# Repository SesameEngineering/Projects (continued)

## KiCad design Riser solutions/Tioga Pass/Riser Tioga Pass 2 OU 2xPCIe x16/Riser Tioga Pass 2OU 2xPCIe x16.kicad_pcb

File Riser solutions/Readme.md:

#Riser Solutions

##Riser solutions for Leopard

###Riser 2 OU, 6x Oculink connector

On this riser we have 6 Oculink connector. Each connector is connected to 4 PCie lanes so we use the 24 PCie lanes available from Leopard server. This riser is used for storage solution since we can connect up to 6 U.2 form factor drives. A special cable, Oculink to U.2 has to be used to connect to each drives. 

###Riser 2 OU, 1x connector PCIe x16 + 2x Oculink connector

On this riser we have 2 Oculink connector and one x16 PCIe connector. Each Oculink uses 4 PCIe lanes so in total we use the 24 PCIe lanes available from Leopard server. Oculink connectors can be connected to U.2 devices via a Oculink to U.2 cable. Any half length PCIe devices can be connected to the x16 PCIe connector (Ava Board, network card, HBA, small form factor GPUs, etc..).

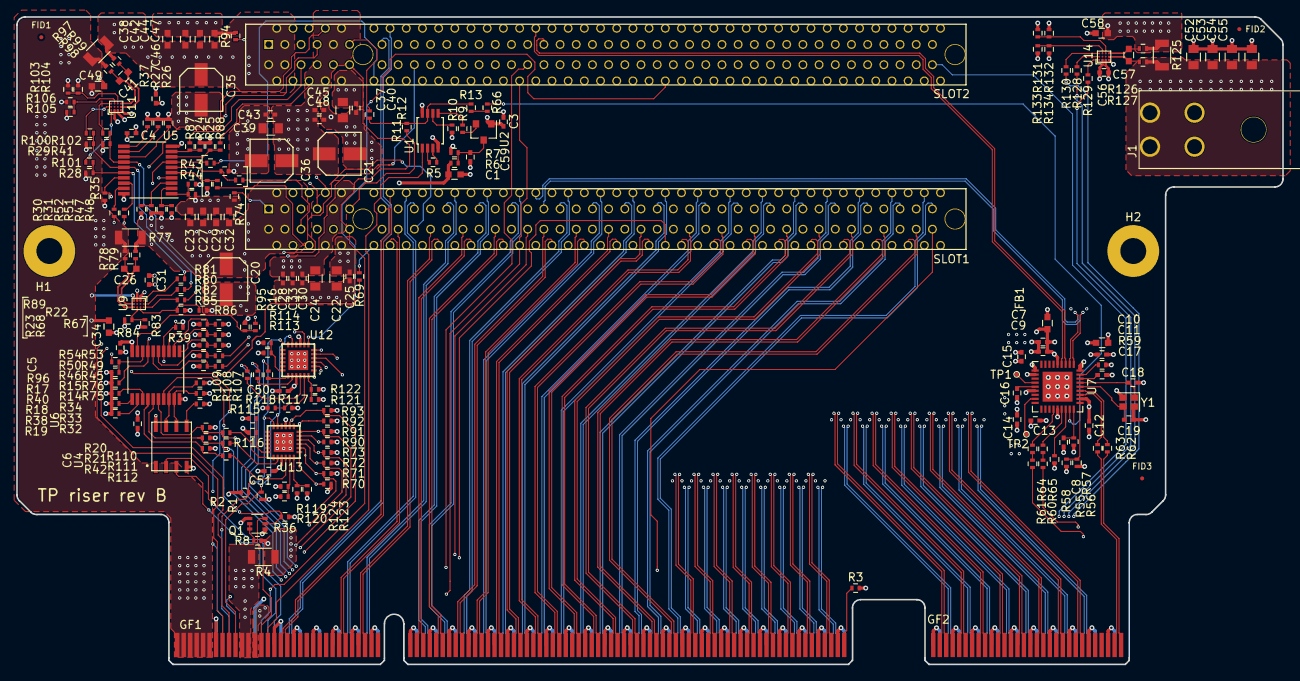
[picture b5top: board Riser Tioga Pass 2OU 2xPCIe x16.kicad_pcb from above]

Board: 6 copper layers, 156.4 x 80.0 mm, 218 parts (0 on the bottom side), 274 nets.

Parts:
C1, C23, C26, C27, C29, C32, C34, C38, C41, C42, C44, C47, C49, C56, C58: 0.1u 25V; C_0603
C3, C4, C5, C6, C8, C25, C28, C30, C31, C33, C40, C43, C45, C46, C48, C50, C51, C57: 0.1u 16V; C_0402
C7: 1u 6.3V; C_0402
C9, C11, C12, C13, C14, C15: 1u 10V; C_0402
C10: 2.2u 10V; C_0603
C16, C17: 0.1u 10V; C_0402
C18, C19: 18p 50V; C_0402
C20, C21, C35, C36: 100u 16V; CapaElec_100u_16V_5.3x5.3mm
C22, C24, C37, C39: 10u 6.3V; C_0805
C52, C53, C54, C55: 22u 16V; C_0805
C59: 0.01u 16V; C_0402
FB1: 300 Ohm 0.5A; Ferrite_0603
FID1, FID2, FID3: Fiducial; Fiducial_0.5mm_Dia_1mm_Outer
GF1: TiogaPass_GF1; GoldFinger_Samtec_HSEC8-1XXX_200pins
GF2: TiogaPAss_GF2; GoldFinger_Samtec_HSEC8-1XXX_60pins
H1, H2: MountingHole_Pad; MountingHole_3.2mm_M3_Pad
J1: RA_4pins_ATX; Conn_02x02_RA_4.2mm_MiniFitJr
Q1: 2N7002KDW; SOT-363_SC-70-6
R1, R2: 475; R_0402
R3: 100; R_0402
R4: 0; R_1206
R5, R9, R11, R12, R13, R30, R31, R60, R61, R62, R63, R64, R65, R66, R67, R68, R69, R74, R75, R76, R80, R81, R82, R87, R88, R89, R94, R95, R96, R100, R101, R102, R107, R108, R109, R110, R111, R112, R128, R129, R130: 0; R_0402
R6: 8.2k; R_0402
R7: 3.3k; R_0402
R8, R10, R14, R15, R16, R17, R18, R19, R20, R21, R22, R23, R24, R25, R26, R27, R28, R29, R33, R34, R70, R71, R72, R73, R90, R91, R92, R93: 4.7k; R_0402
R32, R35, R36, R37, R38, R39, R40, R41, R42, R43, R44, R45, R46, R47, R48, R49, R50, R51, R52, R53, R54, R57, R83, R84, R85, R86, R103, R104, R105, R106, R113, R114, R115, R116, R117, R118, R119, R120, R121, R122, R123, R124, R131, R132, R133, R134: 10k; R_0402
R55, R56, R58: 100k; R_0402
R59: 12k; R_0402
R77, R97, R125: 0.002; R_1206
R78, R79, R98, R99, R126, R127: 10; R_0402
SLOT1, SLOT2: x16_PCIe_Conn; pcie_16x
TP1: OCS_N1; TestPoint_Pad_D0.5mm
TP2: OCS_N2; TestPoint_Pad_D0.5mm
U1: 74LVC2G08DP-Q100H; TSSOP-8_3x3mm_Pitch0.65mm
U2: TPS3809K33; SOT-23
U4: PCA9515AD,118; SO-8_4.9mmx3.9mm
U5, U6: PCA9544APWR; TSSOP-20_4.4x6.5mm_Pitch0.65mm
U7: USB2512BI-AEZG; QFN-36-1EP_6x6mm_Pitch0.5mm
U9, U11, U14: INA231AIYFFT; DSBGA-12_1.65x1.39mm_Pitch0.4mm
U12, U13: PI4IOE5V9535ZDEX; TQFN-24_4x4mm_Pitch0.5mm
Y1: XTAL 24Mhz; Crystal_SMD_2016-4pin_2.0x1.6mm

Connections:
+3V3: C21.1, C24.1, C28.1, C30.1, C33.1, C36.1, C39.1, C43.1, C45.1, C48.1, R4.1, R8.2, R10.2, SLOT1.A9, SLOT1.A10, SLOT1.B8, SLOT2.A9, SLOT2.A10, SLOT2.B8
+3V3_MB: GF1.21, GF1.22, GF1.23, GF1.24, R4.2
+3V3_STBY: C3.2, C4.1, C5.1, C6.1, C22.1, C25.1, C31.1, C37.1, C40.1, C46.1, C50.1, C51.1, C57.1, FB1.2, GF1.25, R14.1, R15.1, R16.1, R17.1, R18.1, R19.1, R20.1, R21.1, R22.1, R23.1, R24.1, R25.1, R26.1, R27.1, R28.1, R29.1, R32.1, R33.1, R34.1, R35.1, R36.1, R37.1, R38.1, R39.1, R40.1, R41.1, R42.1, R43.1, R45.1, R47.1, R49.1, R51.1, R53.1, R70.1, R71.1, R72.1, R73.1, R83.1, R85.1, R90.1, R91.1, R92.1, R93.1, R103.1, R105.1, R113.1, R115.1, R117.1, R119.1, R121.1, R123.1, R131.1, R133.1, SLOT1.B10, SLOT2.B10, U1.8, U4.8, U5.20, U6.20, U9.B1, U11.B1, U12.21, U13.21, U14.B1
+3V3_USB_HUB: C7.1, C9.1, C10.1, C11.1, C12.1, C13.1, C14.1, C15.1, FB1.1, R55.1, R57.1, U7.5, U7.10, U7.15, U7.23, U7.29, U7.36
+12V: C1.1, C34.1, C49.1, C58.1, GF1.1, GF1.2, GF1.3, GF1.4, GF1.5, GF1.6, GF1.7, GF1.8, GF1.9, GF1.10, GF1.11, GF1.12, R6.1, R77.2, R78.2, R97.1, R98.2, R125.1, R126.2, U9.D1, U11.D1, U14.D1
+12V_ATX: C52.1, C53.1, C54.1, C55.1, J1.3, J1.4, R125.2, R127.2
+12V_SLOT2: C20.1, C23.1, C27.1, C29.1, C32.1, R77.1, R79.2, SLOT1.A2, SLOT1.A3, SLOT1.B1, SLOT1.B2, SLOT1.B3
+12V_SLOT3: C35.1, C38.1, C42.1, C44.1, C47.1, R97.2, R99.2, SLOT2.A2, SLOT2.A3, SLOT2.B1, SLOT2.B2, SLOT2.B3
/ATX Power/ATX_P12V_SENSE_R_V+: C56.1, R126.1, U14.D3
/ATX Power/ATX_P12V_SENSE_R_V-: C56.2, R127.1, U14.D2
/ATX Power/ATX_VMONITOR_A0: R133.2, R134.1, U14.B3
/ATX Power/ATX_VMONITOR_A1: R131.2, R132.1, U14.C3
/GPIO expander/GPIO_B_EXP_A0: R113.2, R114.1, U12.18
/GPIO expander/GPIO_B_EXP_A1: R117.2, R118.1, U12.23
/GPIO expander/GPIO_B_EXP_A2: R121.2, R122.1, U12.24
/GPIO expander/GPIO_P_EXP_A0: R115.2, R116.1, U13.18
/GPIO expander/GPIO_P_EXP_A1: R119.2, R120.1, U13.23
/GPIO expander/GPIO_P_EXP_A2: R123.2, R124.1, U13.24
/Golden Finger/PERST_N_1: R5.2, U1.3
/Golden Finger/PERST_SLOT_N: R11.2, R12.2, R13.2, U1.7
/SMBUS MUX/SMB_B_HUB_A0: R43.2, R44.1, U5.1
/SMBUS MUX/SMB_B_HUB_A1: R47.2, R48.1, U5.2
/SMBUS MUX/SMB_B_HUB_A2: R51.2, R52.1, U5.3
/SMBUS MUX/SMB_P_HUB_A0: R45.2, R46.1, U6.1
/SMBUS MUX/SMB_P_HUB_A1: R49.2, R50.1, U6.2
/SMBUS MUX/SMB_P_HUB_A2: R53.2, R54.1, U6.3
/USB HUB/CFG_SEL1: R58.1, U7.25
/USB HUB/CRFILT: C16.1, U7.14
/USB HUB/NON_REM0: R55.2, R56.1, U7.28
/USB HUB/PLLFILT: C17.1, U7.34
/USB HUB/RBIAS: R59.1, U7.35
/USB HUB/SMCLK_USB_HUB: R60.1, R65.1
/USB HUB/SMDAT_USB_HUB: R61.1, R64.1
/USB HUB/USB2_P02_-R_D+: R62.1, U7.31
/USB HUB/USB2_P02_-R_D-: R63.1, U7.30
/USB HUB/USB_HUB_XTAL_IN: C18.1, U7.33, Y1.1
/USB HUB/USB_HUB_XTAL_OUT: C19.1, U7.32, Y1.3
/USB HUB/VBUS_DET: C8.1, R57.2, U7.27
/x16 PCIe Slot 2 (lower)/SLOT2_P12V_SENSE_R_V+: C26.1, R78.1, U9.D3
/x16 PCIe Slot 2 (lower)/SLOT2_P12V_SENSE_R_V-: C26.2, R79.1, U9.D2
/x16 PCIe Slot 2 (lower)/SLOT2_VMONITOR_A0: R85.2, R86.1, U9.B3
/x16 PCIe Slot 2 (lower)/SLOT2_VMONITOR_A1: R83.2, R84.1, U9.C3
/x16 PCIe Slot 3 (upper)/SLOT3_P12V_SENSE_R_V+: C41.1, R98.1, U11.D3
/x16 PCIe Slot 3 (upper)/SLOT3_P12V_SENSE_R_V-: C41.2, R99.1, U11.D2
/x16 PCIe Slot 3 (upper)/SLOT3_VMONITOR_A0: R105.2, R106.1, U11.B3
/x16 PCIe Slot 3 (upper)/SLOT3_VMONITOR_A1: R103.2, R104.1, U11.C3
CLK_100M_PCH_SLOTX24_S4_D+: GF1.36, SLOT2.A13
CLK_100M_PCH_SLOTX24_S4_D-: GF1.38, SLOT2.A14
CLK_100M_PCH_SLOTX24_S5_D+: GF1.33, SLOT1.A13
CLK_100M_PCH_SLOTX24_S5_D-: GF1.35, SLOT1.A14
FM_PE_SLOTX24_WAKE_N: GF1.28, SLOT1.B11, SLOT2.B11
FM_PRSNT_2_6_N: GF1.199, R3.1
FM_PWRBRK_SLOT_N: GF1.20, SLOT1.B30, SLOT2.B30
FM_SLT_CFG0: GF1.19, R1.1, U12.11, U13.11
FM_SLT_CFG1: GF1.18, R2.1, U12.12, U13.12
GND: C1.2, C3.1, C4.2, C5.2, C6.2, C7.2, C8.2, C9.2, C10.2, C11.2, C12.2, C13.2, C14.2, C15.2, C16.2, C17.2, C18.2, C19.2, C20.2, C21.2, C22.2, C23.2, C24.2, C25.2, C27.2, C28.2, C29.2, C30.2, C31.2, C32.2, C33.2, C34.2, C35.2, C36.2, C37.2, C38.2, C39.2, C40.2, C42.2, C43.2, C44.2, C45.2, C46.2, C47.2, C48.2, C49.2, C50.2, C51.2, C52.2, C53.2, C54.2, C55.2, C57.2, C58.2, C59.2, GF1.13, GF1.14, GF1.26, GF1.31, GF1.34, GF1.37, GF1.40, GF1.43, GF1.46, GF1.49, GF1.52, GF1.55, GF1.58, GF1.61, GF1.64, GF1.65, GF1.68, GF1.71, GF1.74, GF1.77, GF1.80, GF1.83, GF1.86, GF1.89, GF1.92, GF1.95, GF1.98, GF1.101, GF1.104, GF1.107, GF1.110, GF1.113, GF1.116, GF1.119, GF1.122, GF1.125, GF1.128, GF1.131, GF1.134, GF1.137, GF1.140, GF1.143, GF1.146, GF1.149, GF1.152, GF1.155, GF1.158, GF1.161, GF1.164, GF1.167, GF1.170, GF1.173, GF1.176, GF1.179, GF1.182, GF1.185, GF1.188, GF1.191, GF1.194, GF1.197, GF1.200, GF2.1, GF2.4, GF2.7, GF2.10, GF2.13, GF2.16, GF2.19, GF2.22, GF2.25, GF2.28, GF2.31, GF2.34, GF2.37, GF2.40, GF2.43, GF2.46, GF2.49, GF2.52, GF2.55, GF2.58, H1.1, H2.1, J1.1, J1.2, Q1.1, Q1.4, R1.2, R2.2, R3.2, R7.2, R44.2, R46.2, R48.2, R50.2, R52.2, R54.2, R56.2, R58.2, R59.2, R74.1, R84.2, R86.2, R94.1, R104.2, R106.2, R114.2, R116.2, R118.2, R120.2, R122.2, R124.2, R132.2, R134.2, SLOT1.A4, SLOT1.A12, SLOT1.A15, SLOT1.A18, SLOT1.A20, SLOT1.A23, SLOT1.A24, SLOT1.A27, SLOT1.A28, SLOT1.A31, SLOT1.A34, SLOT1.A37, SLOT1.A38, SLOT1.A41, SLOT1.A42, SLOT1.A45, SLOT1.A46, SLOT1.A49, SLOT1.A51, SLOT1.A54, SLOT1.A55, SLOT1.A58, SLOT1.A59, SLOT1.A62, SLOT1.A63, SLOT1.A66, SLOT1.A67, SLOT1.A70, SLOT1.A71, SLOT1.A74, SLOT1.A75, SLOT1.A78, SLOT1.A79, SLOT1.A82, SLOT1.B4, SLOT1.B7, SLOT1.B13, SLOT1.B16, SLOT1.B18, SLOT1.B21, SLOT1.B22, SLOT1.B25, SLOT1.B26, SLOT1.B29, SLOT1.B32, SLOT1.B35, SLOT1.B36, SLOT1.B39, SLOT1.B40, SLOT1.B43, SLOT1.B44, SLOT1.B47, SLOT1.B49, SLOT1.B52, SLOT1.B53, SLOT1.B56, SLOT1.B57, SLOT1.B60, SLOT1.B61, SLOT1.B64, SLOT1.B65, SLOT1.B68, SLOT1.B69, SLOT1.B72, SLOT1.B73, SLOT1.B76, SLOT1.B77, SLOT1.B80, SLOT2.A4, SLOT2.A12, SLOT2.A15, SLOT2.A18, SLOT2.A20, SLOT2.A23, SLOT2.A24, SLOT2.A27, SLOT2.A28, SLOT2.A31, SLOT2.A34, SLOT2.A37, SLOT2.A38, SLOT2.A41, SLOT2.A42, SLOT2.A45, SLOT2.A46, SLOT2.A49, SLOT2.A51, SLOT2.A54, SLOT2.A55, SLOT2.A58, SLOT2.A59, SLOT2.A62, SLOT2.A63, SLOT2.A66, SLOT2.A67, SLOT2.A70, SLOT2.A71, SLOT2.A74, SLOT2.A75, SLOT2.A78, SLOT2.A79, SLOT2.A82, SLOT2.B4, SLOT2.B7, SLOT2.B13, SLOT2.B16, SLOT2.B18, SLOT2.B21, SLOT2.B22, SLOT2.B25, SLOT2.B26, SLOT2.B29, SLOT2.B32, SLOT2.B35, SLOT2.B36, SLOT2.B39, SLOT2.B40, SLOT2.B43, SLOT2.B44, SLOT2.B47, SLOT2.B49, SLOT2.B52, SLOT2.B53, SLOT2.B56, SLOT2.B57, SLOT2.B60, SLOT2.B61, SLOT2.B64, SLOT2.B65, SLOT2.B68, SLOT2.B69, SLOT2.B72, SLOT2.B73, SLOT2.B76, SLOT2.B77, SLOT2.B80, U1.4, U2.1, U4.4, U5.10, U6.10, U7.11, U7.37, U9.C1, U11.C1, U12.9, U12.25, U13.9, U13.25, U14.C1, Y1.2, Y1.4
IRQ_OOB_MGMT_RISER_ALERT_N: GF1.16, R35.2, U5.17
unnamed: C59.1, R6.2, R7.1, U2.3
unnamed: Q1.5, Q1.6, R8.1
unnamed: R5.1, U1.2
unnamed: R9.1, U1.5
unnamed: R9.2, U2.2
unnamed: R10.1, U1.6
unnamed: R30.1, U5.19
unnamed: R31.1, U5.18
unnamed: R64.2, U7.22
unnamed: R65.2, U7.24
unnamed: R66.2, U7.26
unnamed: R67.1, SLOT1.B5
unnamed: R68.1, SLOT1.B6
unnamed: R69.1, SLOT1.B12
unnamed: R74.2, SLOT1.A1
unnamed: R75.2, SLOT1.A7
unnamed: R76.2, SLOT1.A8
unnamed: R80.1, U9.A2
unnamed: R81.1, U9.A1
unnamed: R82.2, U9.A3
unnamed: R87.1, SLOT2.B5
unnamed: R88.1, SLOT2.B6
unnamed: R89.1, SLOT2.B12
unnamed: R94.2, SLOT2.A1
unnamed: R95.2, SLOT2.A7
unnamed: R96.2, SLOT2.A8
unnamed: R100.1, U11.A2
unnamed: R101.1, U11.A1
unnamed: R102.2, U11.A3
unnamed: R107.2, U12.19
unnamed: R108.2, U12.20
unnamed: R109.2, U12.22
unnamed: R110.2, U13.19
unnamed: R111.2, U13.20
unnamed: R112.2, U13.22
unnamed: R128.1, U14.A2
unnamed: R129.1, U14.A1
unnamed: R130.2, U14.A3
unnamed: TP1.1, U7.13
unnamed: TP2.1, U7.17
P3E_CPU0_PE1_PCH_CON_RX8+: GF1.100, SLOT1.A47
P3E_CPU0_PE1_PCH_CON_RX8-: GF1.102, SLOT1.A48
P3E_CPU0_PE1_PCH_CON_RX9+: GF1.94, SLOT1.A43
P3E_CPU0_PE1_PCH_CON_RX9-: GF1.96, SLOT1.A44
P3E_CPU0_PE1_PCH_CON_RX10+: GF1.88, SLOT1.A39
P3E_CPU0_PE1_PCH_CON_RX10-: GF1.90, SLOT1.A40
P3E_CPU0_PE1_PCH_CON_RX11+: GF1.82, SLOT1.A35
P3E_CPU0_PE1_PCH_CON_RX11-: GF1.84, SLOT1.A36
P3E_CPU0_PE1_PCH_CON_RX12+: GF1.76, SLOT1.A29
P3E_CPU0_PE1_PCH_CON_RX12-: GF1.78, SLOT1.A30
P3E_CPU0_PE1_PCH_CON_RX13+: GF1.70, SLOT1.A25
P3E_CPU0_PE1_PCH_CON_RX13-: GF1.72, SLOT1.A26
P3E_CPU0_PE1_PCH_CON_RX14+: GF1.60, SLOT1.A21
P3E_CPU0_PE1_PCH_CON_RX14-: GF1.62, SLOT1.A22
P3E_CPU0_PE1_PCH_CON_RX15+: GF1.54, SLOT1.A16
P3E_CPU0_PE1_PCH_CON_RX15-: GF1.56, SLOT1.A17
P3E_CPU0_PE1_PCH_CON_TX8+: GF1.97, SLOT1.B45
P3E_CPU0_PE1_PCH_CON_TX8-: GF1.99, SLOT1.B46
P3E_CPU0_PE1_PCH_CON_TX9+: GF1.91, SLOT1.B41
P3E_CPU0_PE1_PCH_CON_TX9-: GF1.93, SLOT1.B42
P3E_CPU0_PE1_PCH_CON_TX10+: GF1.85, SLOT1.B37
P3E_CPU0_PE1_PCH_CON_TX10-: GF1.87, SLOT1.B38
P3E_CPU0_PE1_PCH_CON_TX11+: GF1.79, SLOT1.B33
P3E_CPU0_PE1_PCH_CON_TX11-: GF1.81, SLOT1.B34
P3E_CPU0_PE1_PCH_CON_TX12+: GF1.73, SLOT1.B27
P3E_CPU0_PE1_PCH_CON_TX12-: GF1.75, SLOT1.B28
P3E_CPU0_PE1_PCH_CON_TX13+: GF1.67, SLOT1.B23
P3E_CPU0_PE1_PCH_CON_TX13-: GF1.69, SLOT1.B24
P3E_CPU0_PE1_PCH_CON_TX14+: GF1.57, SLOT1.B19
P3E_CPU0_PE1_PCH_CON_TX14-: GF1.59, SLOT1.B20
P3E_CPU0_PE1_PCH_CON_TX15+: GF1.51, SLOT1.B14
P3E_CPU0_PE1_PCH_CON_TX15-: GF1.53, SLOT1.B15
P3E_CPU0_PE1_SS_C_RX0+: GF1.148, SLOT1.A80
P3E_CPU0_PE1_SS_C_RX0-: GF1.150, SLOT1.A81
P3E_CPU0_PE1_SS_C_RX1+: GF1.142, SLOT1.A76
P3E_CPU0_PE1_SS_C_RX1-: GF1.144, SLOT1.A77
P3E_CPU0_PE1_SS_C_RX2+: GF1.136, SLOT1.A72
P3E_CPU0_PE1_SS_C_RX2-: GF1.138, SLOT1.A73
P3E_CPU0_PE1_SS_C_RX3+: GF1.130, SLOT1.A68
P3E_CPU0_PE1_SS_C_RX3-: GF1.132, SLOT1.A69
P3E_CPU0_PE1_SS_C_RX4+: GF1.124, SLOT1.A64
P3E_CPU0_PE1_SS_C_RX4-: GF1.126, SLOT1.A65
P3E_CPU0_PE1_SS_C_RX5+: GF1.118, SLOT1.A60
P3E_CPU0_PE1_SS_C_RX5-: GF1.120, SLOT1.A61
P3E_CPU0_PE1_SS_C_RX6+: GF1.112, SLOT1.A56
P3E_CPU0_PE1_SS_C_RX6-: GF1.114, SLOT1.A57
P3E_CPU0_PE1_SS_C_RX7+: GF1.106, SLOT1.A52
P3E_CPU0_PE1_SS_C_RX7-: GF1.108, SLOT1.A53
P3E_CPU0_PE1_SS_C_TX0+: GF1.145, SLOT1.B78
P3E_CPU0_PE1_SS_C_TX0-: GF1.147, SLOT1.B79
P3E_CPU0_PE1_SS_C_TX1+: GF1.139, SLOT1.B74
P3E_CPU0_PE1_SS_C_TX1-: GF1.141, SLOT1.B75
P3E_CPU0_PE1_SS_C_TX2+: GF1.133, SLOT1.B70
P3E_CPU0_PE1_SS_C_TX2-: GF1.135, SLOT1.B71
P3E_CPU0_PE1_SS_C_TX3+: GF1.127, SLOT1.B66
P3E_CPU0_PE1_SS_C_TX3-: GF1.129, SLOT1.B67
P3E_CPU0_PE1_SS_C_TX4+: GF1.121, SLOT1.B62
P3E_CPU0_PE1_SS_C_TX4-: GF1.123, SLOT1.B63
P3E_CPU0_PE1_SS_C_TX5+: GF1.115, SLOT1.B58
P3E_CPU0_PE1_SS_C_TX5-: GF1.117, SLOT1.B59
P3E_CPU0_PE1_SS_C_TX6+: GF1.109, SLOT1.B54
P3E_CPU0_PE1_SS_C_TX6-: GF1.111, SLOT1.B55
P3E_CPU0_PE1_SS_C_TX7+: GF1.103, SLOT1.B50
P3E_CPU0_PE1_SS_C_TX7-: GF1.105, SLOT1.B51
P3E_CPU0_PE2_SS_C_RX0+: GF1.154, SLOT2.A16
P3E_CPU0_PE2_SS_C_RX0-: GF1.156, SLOT2.A17
P3E_CPU0_PE2_SS_C_RX1+: GF1.160, SLOT2.A21
P3E_CPU0_PE2_SS_C_RX1-: GF1.162, SLOT2.A22
P3E_CPU0_PE2_SS_C_RX2+: GF1.166, SLOT2.A25
P3E_CPU0_PE2_SS_C_RX2-: GF1.168, SLOT2.A26
P3E_CPU0_PE2_SS_C_RX3+: GF1.172, SLOT2.A29
P3E_CPU0_PE2_SS_C_RX3-: GF1.174, SLOT2.A30
P3E_CPU0_PE2_SS_C_RX4+: GF1.178, SLOT2.A35
P3E_CPU0_PE2_SS_C_RX4-: GF1.180, SLOT2.A36
P3E_CPU0_PE2_SS_C_RX5+: GF1.184, SLOT2.A39
P3E_CPU0_PE2_SS_C_RX5-: GF1.186, SLOT2.A40
P3E_CPU0_PE2_SS_C_RX6+: GF1.190, SLOT2.A43
P3E_CPU0_PE2_SS_C_RX6-: GF1.192, SLOT2.A44
P3E_CPU0_PE2_SS_C_RX7+: GF1.196, SLOT2.A47
P3E_CPU0_PE2_SS_C_RX7-: GF1.198, SLOT2.A48
P3E_CPU0_PE2_SS_C_RX8+: GF2.6, SLOT2.A52
P3E_CPU0_PE2_SS_C_RX8-: GF2.8, SLOT2.A53
P3E_CPU0_PE2_SS_C_RX9+: GF2.12, SLOT2.A56
P3E_CPU0_PE2_SS_C_RX9-: GF2.14, SLOT2.A57
P3E_CPU0_PE2_SS_C_RX10+: GF2.18, SLOT2.A60
P3E_CPU0_PE2_SS_C_RX10-: GF2.20, SLOT2.A61
P3E_CPU0_PE2_SS_C_RX11+: GF2.24, SLOT2.A64
P3E_CPU0_PE2_SS_C_RX11-: GF2.26, SLOT2.A65
P3E_CPU0_PE2_SS_C_RX12+: GF2.30, SLOT2.A68
P3E_CPU0_PE2_SS_C_RX12-: GF2.32, SLOT2.A69
P3E_CPU0_PE2_SS_C_RX13+: GF2.36, SLOT2.A72
P3E_CPU0_PE2_SS_C_RX13-: GF2.38, SLOT2.A73
P3E_CPU0_PE2_SS_C_RX14+: GF2.42, SLOT2.A76
P3E_CPU0_PE2_SS_C_RX14-: GF2.44, SLOT2.A77
P3E_CPU0_PE2_SS_C_RX15+: GF2.48, SLOT2.A80
P3E_CPU0_PE2_SS_C_RX15-: GF2.50, SLOT2.A81
P3E_CPU0_PE2_SS_C_TX0+: GF1.151, SLOT2.B14
P3E_CPU0_PE2_SS_C_TX0-: GF1.153, SLOT2.B15
P3E_CPU0_PE2_SS_C_TX1+: GF1.157, SLOT2.B19
P3E_CPU0_PE2_SS_C_TX1-: GF1.159, SLOT2.B20
P3E_CPU0_PE2_SS_C_TX2+: GF1.163, SLOT2.B23
P3E_CPU0_PE2_SS_C_TX2-: GF1.165, SLOT2.B24
P3E_CPU0_PE2_SS_C_TX3+: GF1.169, SLOT2.B27
P3E_CPU0_PE2_SS_C_TX3-: GF1.171, SLOT2.B28
P3E_CPU0_PE2_SS_C_TX4+: GF1.175, SLOT2.B33
P3E_CPU0_PE2_SS_C_TX4-: GF1.177, SLOT2.B34
P3E_CPU0_PE2_SS_C_TX5+: GF1.181, SLOT2.B37
P3E_CPU0_PE2_SS_C_TX5-: GF1.183, SLOT2.B38
P3E_CPU0_PE2_SS_C_TX6+: GF1.187, SLOT2.B41
P3E_CPU0_PE2_SS_C_TX6-: GF1.189, SLOT2.B42
P3E_CPU0_PE2_SS_C_TX7+: GF1.193, SLOT2.B45
P3E_CPU0_PE2_SS_C_TX7-: GF1.195, SLOT2.B46
P3E_CPU0_PE2_SS_C_TX8+: GF2.3, SLOT2.B50
P3E_CPU0_PE2_SS_C_TX8-: GF2.5, SLOT2.B51
P3E_CPU0_PE2_SS_C_TX9+: GF2.9, SLOT2.B54
P3E_CPU0_PE2_SS_C_TX9-: GF2.11, SLOT2.B55
P3E_CPU0_PE2_SS_C_TX10+: GF2.15, SLOT2.B58
P3E_CPU0_PE2_SS_C_TX10-: GF2.17, SLOT2.B59
P3E_CPU0_PE2_SS_C_TX11+: GF2.21, SLOT2.B62
P3E_CPU0_PE2_SS_C_TX11-: GF2.23, SLOT2.B63
P3E_CPU0_PE2_SS_C_TX12+: GF2.27, SLOT2.B66
P3E_CPU0_PE2_SS_C_TX12-: GF2.29, SLOT2.B67
P3E_CPU0_PE2_SS_C_TX13+: GF2.33, SLOT2.B70
P3E_CPU0_PE2_SS_C_TX13-: GF2.35, SLOT2.B71
P3E_CPU0_PE2_SS_C_TX14+: GF2.39, SLOT2.B74
P3E_CPU0_PE2_SS_C_TX14-: GF2.41, SLOT2.B75
P3E_CPU0_PE2_SS_C_TX15+: GF2.45, SLOT2.B78
P3E_CPU0_PE2_SS_C_TX15-: GF2.47, SLOT2.B79
PCIE_SLOT2_PRSNT2_1_N: R70.2, SLOT1.B17, U12.1, U13.1
PCIE_SLOT2_PRSNT2_2_N: R71.2, SLOT1.B31, U12.2, U13.2
PCIE_SLOT2_PRSNT2_3_N: R72.2, SLOT1.B48, U12.3, U13.3
PCIE_SLOT2_PRSNT2_4_N: R73.2, SLOT1.B81, U12.4, U13.4
PCIE_SLOT3_PRSNT2_1_N: R90.2, SLOT2.B17, U12.5, U13.5
PCIE_SLOT3_PRSNT2_2_N: R91.2, SLOT2.B31, U12.6, U13.6
PCIE_SLOT3_PRSNT2_3_N: R92.2, SLOT2.B48, U12.7, U13.7
PCIE_SLOT3_PRSNT2_4_N: R93.2, SLOT2.B81, U12.8, U13.8
PERST_N: GF1.29, U1.1
PU_B_MUX_SCL2: R26.2, U5.13
PU_B_MUX_SDA2: R27.2, U5.12
PU_I2CMUX_INT2_N: R37.2, U5.11
PU_P_I2CMUX_INT2_N: R38.2, U6.11
PU_P_MUX_SCL2: R18.2, U6.13
PU_P_MUX_SDA2: R19.2, U6.12
RESET_BUF_N_SLOT2: R11.1, SLOT1.A11
RESET_BUF_N_SLOT3: R12.1, SLOT2.A11
SMBCLK_PCH_R: R34.2, U4.7, U6.18
SMBDAT_PCH_R: R33.2, U4.6, U6.19
SMB_BMC_DEVICE_ALERT_N: R41.2, R82.1, R102.1, R109.1, R130.1, U5.14
SMB_HOST_STBY_LVC3_SCL_R5: GF1.32, U4.2
SMB_HOST_STBY_LVC3_SDA_R5: GF1.30, U4.3
SMB_PCH_ALERT_N: Q1.2, R36.2, U6.17
SMB_PCH_ALERT_R_N: GF1.27, Q1.3
SMB_PCH_DEVICE_ALERT_N: R42.2, R112.1, U6.14
SMB_PCIE_SLOT2_ALERT_N: R39.2, R69.2, U5.4, U6.4
SMB_PCIE_SLOT3_ALERT_N: R40.2, R89.2, U5.7, U6.7
SMB_P_REPEATER_EN: R32.2, U4.5
SMB_SLOTX24_STBY_LVC3_SCL: GF1.17, R31.2
SMB_SLOTX24_STBY_LVC3_SDA: GF1.15, R30.2
SMCLK_BMC_DEVICE: R28.2, R81.2, R101.2, R107.1, R129.2, U5.16
SMCLK_BMC_SLOT2: R22.2, R67.2, U5.6
SMCLK_BMC_SLOT3: R24.2, R87.2, U5.9
SMCLK_PCH_DEVICE: R20.2, R60.2, R110.1, U6.16
SMCLK_PCH_SLOT2: R14.2, R75.1, U6.6
SMCLK_PCH_SLOT3: R16.2, R95.1, U6.9
SMDAT_BMC_DEVICE: R29.2, R80.2, R100.2, R108.1, R128.2, U5.15
SMDAT_BMC_SLOT2: R23.2, R68.2, U5.5
SMDAT_BMC_SLOT3: R25.2, R88.2, U5.8
SMDAT_PCH_DEVICE: R21.2, R61.2, R111.1, U6.15
SMDAT_PCH_SLOT2: R15.2, R76.1, U6.5
SMDAT_PCH_SLOT3: R17.2, R96.1, U6.8
USB2_P02_D+: GF2.59, R62.2
USB2_P02_D-: GF2.57, R63.2
USB_HUB_PCIE_D0+: SLOT1.A32, U7.2
USB_HUB_PCIE_D0-: SLOT1.A33, U7.1
USB_HUB_PCIE_D1+: SLOT2.A32, U7.4
USB_HUB_PCIE_D1-: SLOT2.A33, U7.3
USB_RESET_N: R13.1, R66.1

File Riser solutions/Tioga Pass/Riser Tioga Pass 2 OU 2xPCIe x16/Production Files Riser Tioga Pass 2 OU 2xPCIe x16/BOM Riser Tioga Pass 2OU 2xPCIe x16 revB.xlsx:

Id | Reference | Footprint | Quantity | Designation | Manufacturer | Manufacturer part number | Comments
1 | C1,C23,C26,C27,C29,C32,C34,C38,C41,C42,C44,C47,C49,C56,C58 | C_0603 | 15 | 0.1u 25V | KEMET | C0603C104K3RAC7013
2 | C3,C4,C5,C6,C8,C25,C28,C30,C31,C33,C40,C43,C45,C46,C48,C50,C51,C57 | C_0402 | 19 | 0.1u 16V | Murata Electronics | GCM155R71C104KA55D
3 | C7 | C_0402 | 1 | 1u 6.3V | Taiyo Yuden | JMK105BJ105KV-F
4 | C9,C11,C12,C13,C14,C15 | C_0402 | 6 | 1u 10V | YAGEO | CC0402KRX5R6BB105
5 | C10 | C_0603 | 1 | 2.2u 10V | Murata Electronics | GRM188R71A225KE15D
6 | C16,C17 | C_0402 | 2 | 0.1u 10V | Taiyo Yuden | LMF105B7104KVHF
7 | C18,C19 | C_0402 | 2 | 18p 50V | KEMET | C0402C180J5GAC7411
8 | C20,C21,C35,C36 | CapaElec_100u_16V_5.3x5.3mm | 4 | 100u 16V | Panasonic | EEE-FK1C101SR
9 | C22,C24,C37,C39 | C_0805 | 4 | 10u 6.3V | Taiyo Yuden | JMF212AB7106KGHT
10 | C52,C53,C54,C55 | C_0805 | 4 | 22u 16V | Samsung Electro-Mechanics | CL21A226KOQNNNG
11 | C59 | C_0402 | 1 | 0.01u 16V | Taiyo Yuden | EMF105B7103KVHF
12 | FB1 | Ferrite_0603 | 1 | 300 Ohm 0.5A | TDK | MMZ1608B301CTAH0
13 | J1 | Conn_02x02_RA_4.2mm_MiniFitJr | 1 | RA_4pins_ATX | Molex | 39-30-0040
14 | Q1 | SOT-363_SC-70-6 | 1 | 2N7002KDW | Panjit | 2N7002KDW_R1_00001
15 | R1,R2 | R_0402 | 2 | 475 | YAGEO | AC0402FR-07475RL
16 | R3 | R_0402 | 1 | 100 | Vishay / Beyschlag | MCS04020D1000BE000
17 | R4 | R_1206 | 1 | 0 | YAGEO | RC1206FR-070RL
18 | R5,R9,R11,R12,R13,R30,R31,R60,R61,R62,R63,R64,R65,R66,R67,R68,R69,R74,R75,R76,R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 | R_0402 | 41 | 0 | ROHM Semiconductor | SFR01MZPJ000
19 | R6 | R_0402 | 1 | 8.2k | Panasonic | ERJ-2RKF8201X
20 | R7 | R_0402 | 1 | 3.3k | YAGEO | RC0402FR-073K3L
21 | R8,R10,R14,R15,R16,R17,R18,R19,R20,R21,R22,R23,R24,R25,R26,R27,R28,R29,R33,R34,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 | R_0402 | 28 | 4.7k | YAGEO | RC0402FR-7D4K7L
22 | R32,R35,R36,R37,R38,R39,R40,R41,R42,R43,R44,R45,R46,R47,R48,R49,R50,R51,R52,R53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 | R_0402 | 46 | 10k | Vishay / Dale | CRCW040210K0FKEDC | R44,R47,R51,R46,R49,R53,R83,R85,R103,R106,R113,R117,R122,R115,R119,R124,R132,R1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
23 | R55,R56,R58 | R_0402 | 3 | 100k | Vishay / Dale | CRCW0402100KFKEDC | R55,R56 NOT CONNECTED
24 | R59 | R_0402 | 1 | 12k | Vishay / Dale | CRCW040212K0FKEDC
25 | R77,R97,R125 | R_1206 | 3 | 0.002 | YAGEO | PA1206FRF7W0R002L
26 | R78,R79,R98,R99,R126,R127 | R_0402 | 6 | 10 | Vishay / Dale | CRCW040210R0FKEE
27 | SLOT1,SLOT2 | pcie_16x | 2 | x16_PCIe_Conn | Amphenol FCI | 10018784-10203TLF
28 | U1 | TSSOP-8_3x3mm_Pitch0.65mm | 1 | 74LVC2G08DP-Q100H | Nexperia | 74LVC2G08DP-Q100H
29 | U2 | SOT-23 | 1 | TPS3809K33 | Texas Instruments | TPS3809K33MDBVREP
30 | U4 | SO-8_4.9mmx3.9mm | 1 | PCA9515AD,118 | NXP Semiconductors | PCA9515AD,118
31 | U5,U6 | TSSOP-20_4.4x6.5mm_Pitch0.65mm | 2 | PCA9544APWR | Texas Instruments | PCA9544APWR
32 | U7 | QFN-36-1EP_6x6mm_Pitch0.5mm | 1 | USB2512BI-AEZG | Microchip Technology | USB2512BI-AEZG
33 | U9,U11,U14 | DSBGA-12_1.65x1.39mm_Pitch0.4mm | 3 | INA231AIYFFT | Texas Instruments | INA231AIYFFT
34 | U12,U13 | TQFN-24_4x4mm_Pitch0.5mm | 2 | PI4IOE5V9535ZDEX | Diodes Incorporated | PI4IOE5V9535ZDEX
35 | Y1 | Crystal_SMD_2016-4pin_2.0x1.6mm | 1 | XTAL 24Mhz | ECS | ECS-240-12-37B-7KM-TR
